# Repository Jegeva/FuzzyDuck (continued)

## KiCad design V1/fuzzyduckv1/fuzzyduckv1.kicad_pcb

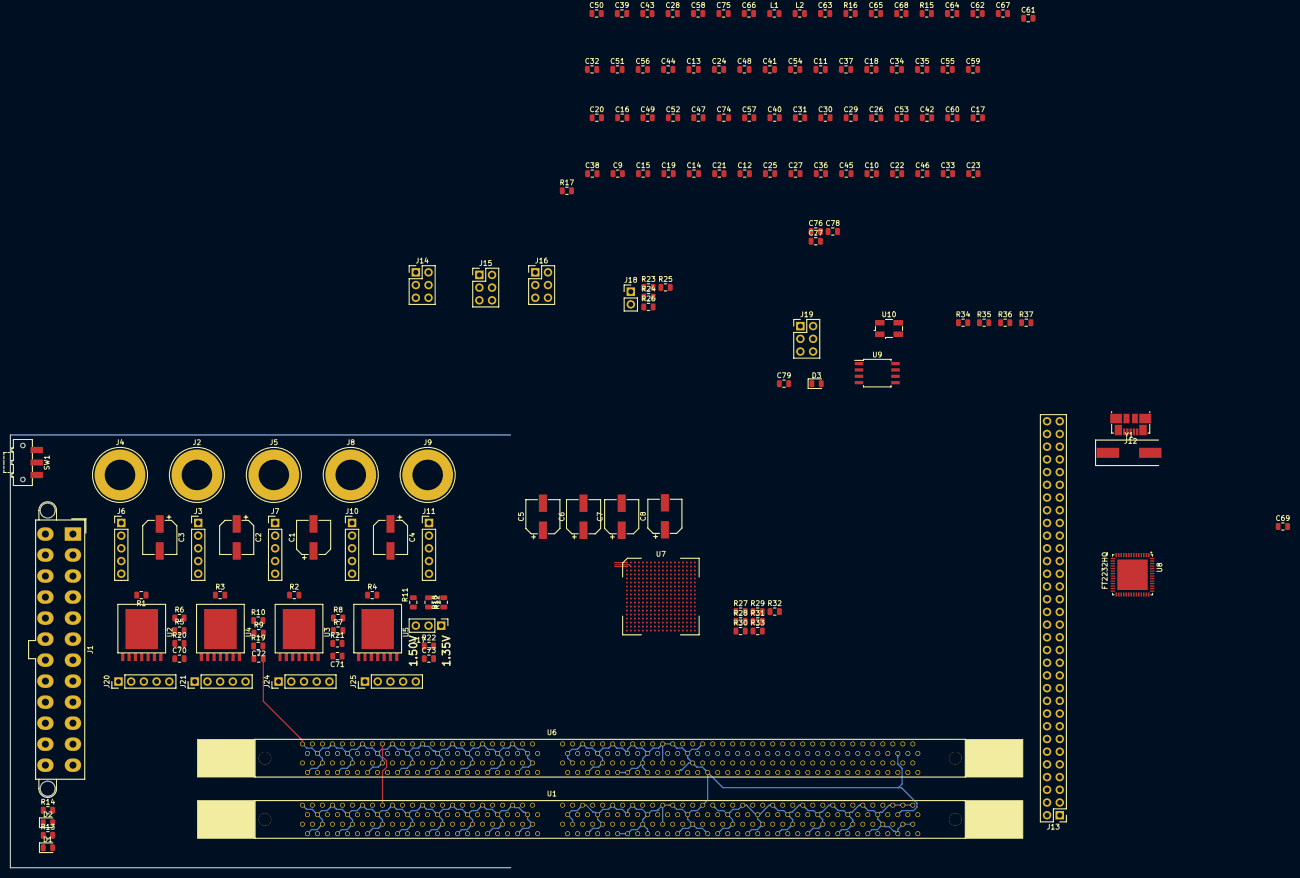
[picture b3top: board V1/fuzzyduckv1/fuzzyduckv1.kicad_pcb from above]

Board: 6 copper layers, 156 parts (0 on the bottom side), 268 nets.

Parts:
C1, C2, C3, C4, C5, C6, C7, C8: 200uF Electrolytic; CP_Elec_6.3x5.4_Nichicon
C9, C10, C11, C77: 47uF X7R; C_0805_2012Metric
C12, C70, C71, C72, C73: 10uF X7R; C_0805_2012Metric
C13, C14, C15, C16: 1uF X7R; C_0805_2012Metric
C17, C18, C19, C20, C21, C22, C23, C24, C25, C26, C27, C28, C29, C30, C31, C32, C33, C34, C35, C36, C37, C38, C39, C40, C41, C42, C43, C44: 100nF X7R; C_0805_2012Metric
C45, C46, C47, C48, C49, C50, C51, C52, C53, C54, C55, C56, C57, C58, C59, C60, C78: 10nF X7R; C_0805_2012Metric
C61, C64: 4.7uF TA; C_0805_2012Metric
C62, C65, C75: 100nF; C_0805_2012Metric
C63, C66, C74: 10nF; C_0805_2012Metric
C67, C68: 20pF; C_0805_2012Metric
C69: 3.3uF; C_0805_2012Metric
C76: 470nF X7R; C_0805_2012Metric
C79: 0.1uF X7R; C_0805_2012Metric
D1, D2, D3: LED; LED_0805_2012Metric
J1: Conn_02x12_Top_Bottom; Molex_Mini-Fit_Jr_5566-24A2_2x12_P4.20mm_Vertical
J2, J4, J5, J8, J9: Conn_01x01_Male; Banana_Jack_1Pin
J3, J6, J7, J10, J11, J20, J21, J24, J25: Conn_01x05; PinHeader_1x05_P2.54mm_Vertical
J12: USB_B_Micro; USB_Micro-B_Molex_47346-0001
J13: Conn_02x32_Odd_Even; PinHeader_2x32_P2.54mm_Vertical
J14, J15, J16, J19: Conn_02x03_Odd_Even; PinHeader_2x03_P2.54mm_Vertical
J17: Conn_01x03_Male; PinHeader_1x03_P2.54mm_Vertical
J18: Conn_01x02_Male; PinHeader_1x02_P2.54mm_Vertical
L1, L2: 600R/100MHz; L_0805_2012Metric
R1, R2, R3, R4: 100k; R_0805_2012Metric
R5, R6, R7, R9, R11: 10K 0.1%; R_0805_2012Metric
R8: 3.83K 0.1%; R_0805_2012Metric
R10: 7.15K 0.1%; R_0805_2012Metric
R12: 5K 0.5%; R_0805_2012Metric
R13, R14: 220; R_0805_2012Metric
R15: 12k; R_0805_2012Metric
R16, R34, R35, R36, R37: 1k; R_0805_2012Metric
R17: 10k; R_0805_2012Metric
R18: 5.9K 0.5%; R_0805_2012Metric
R19, R22: 120; R_0805_2012Metric
R20, R30, R31: 100; R_0805_2012Metric
R21: 180; R_0805_2012Metric
R23, R24, R25, R26, R27, R28, R32, R33: 4.7k; R_0805_2012Metric
R29: 50; R_0805_2012Metric
SW1: SW_SPDT; SW_SPDT_CK-JS102011SAQN
U1, U6: DIMM-240-DDR3; TE-1932000-DIMM-240
U2, U3, U4, U5: MIC69502
U7: XC7A35T-CSG324; BGA-324_15.0x15.0mm_Layout18x18_P0.8mm_Ball0.5mm_Pad0.4mm_N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
U8: FT2232HQ; VQFN-56-ftdi2232h-56q
U9: IS25LP128F; SOIJ-8_5.3x5.3mm_P1.27mm
U10: SiT8008B-100MHz; Crystal_SMD_EuroQuartz_MJ-4Pin_5.0x3.2mm
Y1: Crystal; Crystal_SMD_HC49-SD

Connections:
+1.0V: C5.1, C9.1, C13.1, C17.1, C21.1, C25.1, C29.1, C33.1, C37.1, C41.1, C45.1, C49.1, C53.1, C57.1, C70.1, J20.1, J20.2, J20.3, J20.4, J20.5, R5.1, R20.1, U2.5, U2.6, U7.F8, U7.F10, U7.G7, U7.G9, U7.G11, U7.H8, U7.J7, U7.J11, U7.K8, U7.L7, U7.L11, U7.M8, U7.M10, U7.N7, U7.N9, U7.N11
+1.2V: C7.1, C11.1, C15.1, C19.1, C23.1, C27.1, C31.1, C35.1, C39.1, C43.1, C47.1, C51.1, C55.1, C59.1, C72.1, J14.2, J15.2, J16.2, J19.2, J21.1, J21.2, J21.3, J21.4, J21.5, R9.1, R19.1, U4.5, U4.6
+1.5v: C8.1, C12.1, C16.1, C20.1, C24.1, C28.1, C32.1, C36.1, C40.1, C44.1, C48.1, C52.1, C56.1, C60.1
+1.8V: C6.1, C10.1, C14.1, C18.1, C22.1, C26.1, C30.1, C34.1, C38.1, C42.1, C46.1, C50.1, C54.1, C58.1, C71.1, J24.1, J24.2, J24.3, J24.4, J24.5, R7.1, R21.1, U3.5, U3.6, U7.E8, U7.F12, U7.H12, U7.K12, U7.M12
+3.3V: C76.1, C77.1, C79.2, J1.1, J1.2, J1.12, J1.13, J8.1, J10.1, J10.2, J10.3, J10.4, J10.5, J14.6, J15.6, J16.6, J19.6, L1.1, L2.1, R16.2, R23.1, R25.1, R26.1, R27.2, R30.1, R32.1, R33.1, U7.L17, U7.N13, U7.P16, U7.R9, U7.T12, U7.U15, U7.V18, U8.16, U8.36, U8.44, U8.50, U9.8, U10.4
+5V: C1.1, C2.1, C3.1, C4.1, J1.4, J1.6, J1.21, J1.22, J1.23, J5.1, J7.1, J7.2, J7.3, J7.4, J7.5, U2.2, U2.3, U3.2, U3.3, U4.2, U4.3, U5.2, U5.3
+12V: J1.10, J1.11, J2.1, J3.1, J3.2, J3.3, J3.4, J3.5
-12V: J1.14, J4.1, J6.1, J6.2, J6.3, J6.4, J6.5
ATX_POWEROK: J1.8, R1.2, R2.2, R3.2, R4.2, R14.2
CLK_100MHZ: U7.L18, U10.3
DDR_COM_A0: U1.188, U6.188, U7.B4
DDR_COM_A1: U1.181, U6.181, U7.A4
DDR_COM_A2: U1.61, U6.61, U7.A3
DDR_COM_A3: U1.180, U6.180, U7.B1
DDR_COM_A4: U1.59, U6.59, U7.A1
DDR_COM_A5: U1.58, U6.58, U7.B3
DDR_COM_A6: U1.178, U6.178, U7.B2
DDR_COM_A7: U1.56, U6.56, U7.D5
DDR_COM_A8: U1.177, U6.177, U7.D4
DDR_COM_A9: U1.175, U6.175, U7.E3
DDR_COM_A10: U1.70, U6.70, U7.D3
DDR_COM_A11: U1.55, U6.55, U7.F4
DDR_COM_A12: U1.174, U6.174, U7.F3
DDR_COM_A13: U1.196, U6.196, U7.E2
DDR_COM_A14: U1.172, U6.172, U7.D2
DDR_COM_A15: U1.171, U6.171, U7.H2
DDR_COM_BA0: U1.71, U6.71, U7.G2
DDR_COM_BA1: U1.190, U6.190, U7.C2
DDR_COM_BA2: U1.52, U6.52, U7.C1
DDR_COM_CAS#: U1.74, U6.74, U7.G14
DDR_COM_CB0: U1.39, U6.39, U7.E15
DDR_COM_CB1: U1.40, U6.40, U7.E16
DDR_COM_CB2: U1.45, U6.45, U7.D15
DDR_COM_CB3: U1.46, U6.46, U7.C15
DDR_COM_CB4: U1.158, U6.158, U7.H16
DDR_COM_CB5: U1.159, U6.159, U7.G16
DDR_COM_CB6: U1.164, U6.164, U7.F15
DDR_COM_CB7: U1.165, U6.165, U7.F16
DDR_COM_DQ0: U1.3, U6.3, U7.K6
DDR_COM_DQ1: U1.4, U6.4, U7.L1
DDR_COM_DQ2: U1.9, U6.9, U7.M1
DDR_COM_DQ3: U1.10, U6.10, U7.K3
DDR_COM_DQ4: U1.122, U6.122, U7.L3
DDR_COM_DQ5: U1.123, U6.123, U7.N2
DDR_COM_DQ6: U1.128, U6.128, U7.N1
DDR_COM_DQ7: U1.129, U6.129, U7.M3
DDR_COM_DQ8: U1.12, U6.12, U7.M2
DDR_COM_DQ9: U1.13, U6.13, U7.K5
DDR_COM_DQ10: U1.18, U6.18, U7.L4
DDR_COM_DQ11: U1.19, U6.19, U7.L6
DDR_COM_DQ12: U1.131, U6.131, U7.L5
DDR_COM_DQ13: U1.132, U6.132, U7.U1
DDR_COM_DQ14: U1.137, U6.137, U7.V1
DDR_COM_DQ15: U1.138, U6.138, U7.U4
DDR_COM_DQ16: U1.21, U6.21, U7.U3
DDR_COM_DQ17: U1.22, U6.22, U7.U2
DDR_COM_DQ18: U1.27, U6.27, U7.V2
DDR_COM_DQ19: U1.28, U6.28, U7.V5
DDR_COM_DQ20: U1.140, U6.140, U7.V4
DDR_COM_DQ21: U1.141, U6.141, U7.R3
DDR_COM_DQ22: U1.146, U6.146, U7.T3
DDR_COM_DQ23: U1.147, U6.147, U7.T5
DDR_COM_DQ24: U1.30, U6.30, U7.T4
DDR_COM_DQ25: U1.31, U6.31, U7.N5
DDR_COM_DQ26: U1.36, U6.36, U7.P5
DDR_COM_DQ27: U1.37, U6.37, U7.P4
DDR_COM_DQ28: U1.149, U6.149, U7.P3
DDR_COM_DQ29: U1.150, U6.150, U7.P2
DDR_COM_DQ30: U1.155, U6.155, U7.R2
DDR_COM_DQ31: U1.156, U6.156, U7.M4
DDR_COM_DQ32: U1.81, U6.81, U7.N4
DDR_COM_DQ33: U1.82, U6.82, U7.R1
DDR_COM_DQ34: U1.87, U6.87, U7.T1
DDR_COM_DQ35: U1.88, U6.88, U7.M6
DDR_COM_DQ36: U1.200, U6.200, U7.N6
DDR_COM_DQ37: U1.201, U6.201, U7.R6
DDR_COM_DQ38: U1.206, U6.206, U7.R5
DDR_COM_DQ39: U1.207, U6.207, U7.V7
DDR_COM_DQ40: U1.90, U6.90, U7.V6
DDR_COM_DQ41: U1.91, U6.91, U7.U9
DDR_COM_DQ42: U1.96, U6.96, U7.V9
DDR_COM_DQ43: U1.97, U6.97, U7.U7
DDR_COM_DQ44: U1.209, U6.209, U7.U6
DDR_COM_DQ45: U1.210, U6.210, U7.R7
DDR_COM_DQ46: U1.215, U6.215, U7.T6
DDR_COM_DQ47: U1.216, U6.216, U7.R8
DDR_COM_DQ48: U1.99, U6.99, U7.T8
DDR_COM_DQ49: U1.100, U6.100, U7.U8
DDR_COM_DQ50: U1.105, U6.105, U7.F5
DDR_COM_DQ51: U1.106, U6.106, U7.C6
DDR_COM_DQ52: U1.218, U6.218, U7.C5
DDR_COM_DQ53: U1.219, U6.219, U7.B7
DDR_COM_DQ54: U1.224, U6.224, U7.B6
DDR_COM_DQ55: U1.225, U6.225, U7.A6
DDR_COM_DQ56: U1.108, U6.108, U7.A5
DDR_COM_DQ57: U1.109, U6.109, U7.D8
DDR_COM_DQ58: U1.114, U6.114, U7.C7
DDR_COM_DQ59: U1.115, U6.115, U7.E6
DDR_COM_DQ60: U1.227, U6.227, U7.E5
DDR_COM_DQ61: U1.228, U6.228, U7.E7
DDR_COM_DQ62: U1.233, U6.233, U7.D7
DDR_COM_DQ63: U1.234, U6.234, U7.C4
DDR_COM_DQS0: U1.7, U6.7, U7.H1
DDR_COM_DQS0#: U1.6, U6.6, U7.G1
DDR_COM_DQS1: U1.16, U6.16, U7.F1
DDR_COM_DQS1#: U1.15, U6.15, U7.E1
DDR_COM_DQS2: U1.25, U6.25, U7.G6
DDR_COM_DQS2#: U1.24, U6.24, U7.F6
DDR_COM_DQS3: U1.34, U6.34, U7.G4
DDR_COM_DQS3#: U1.33, U6.33, U7.G3
DDR_COM_DQS4: U1.85, U6.85, U7.J4
DDR_COM_DQS4#: U1.84, U6.84, U7.H4
DDR_COM_DQS5: U1.94, U6.94, U7.J3
DDR_COM_DQS5#: U1.93, U6.93, U7.J2
DDR_COM_DQS6: U1.103, U6.103, U7.K2
DDR_COM_DQS6#: U1.102, U6.102, U7.K1
DDR_COM_DQS7: U1.112, U6.112, U7.H6
DDR_COM_DQS7#: U1.111, U6.111, U7.H5
DDR_COM_DQS8: U1.43, U6.43, U7.D14
DDR_COM_DQS8#: U1.42, U6.42, U7.C14
DDR_COM_DQS9: U1.125, U6.125, U7.B13
DDR_COM_DQS9#: U1.126, U6.126, U7.B14
DDR_COM_DQS10: U1.134, U6.134, U7.C12
DDR_COM_DQS10#: U1.135, U6.135, U7.B12
DDR_COM_DQS11: U1.143, U6.143, U7.B11
DDR_COM_DQS11#: U1.144, U6.144, U7.A11
DDR_COM_DQS12: U1.152, U6.152, U7.F13
DDR_COM_DQS12#: U1.153, U6.153, U7.F14
DDR_COM_DQS13: U1.203, U6.203, U7.D12
DDR_COM_DQS13#: U1.204, U6.204, U7.D13
DDR_COM_DQS14: U1.212, U6.212, U7.B16
DDR_COM_DQS14#: U1.213, U6.213, U7.B17
DDR_COM_DQS15: U1.221, U6.221, U7.A15
DDR_COM_DQS15#: U1.222, U6.222, U7.A16
DDR_COM_DQS16: U1.230, U6.230, U7.A13
DDR_COM_DQS16#: U1.231, U6.231, U7.A14
DDR_COM_DQS17: U1.161, U6.161, U7.B18
DDR_COM_DQS17#: U1.162, U6.162, U7.A18
DDR_COM_ERROUT#: U1.53, U6.53, U7.D17
DDR_COM_EVENT#: U1.187, U6.187, U7.K13
DDR_COM_RAS#: U1.192, U6.192, U7.H14
DDR_COM_RPARIN: U1.68, U6.68, U7.E17
DDR_COM_WE#: U1.73, U6.73, U7.J13
DDR_DIMM0_CK0: U1.184, U7.F18
DDR_DIMM0_CK0#: U1.185, U7.J17
DDR_DIMM0_CK1: U1.63, U7.D18
DDR_DIMM0_CK1#: U1.64, U7.G18
DDR_DIMM0_CKE0: U1.50, U7.J18
DDR_DIMM0_CKE1: U1.169, U7.K15
DDR_DIMM0_ODT0: U1.195, U7.C17
DDR_DIMM0_ODT1: U1.77, U7.C16
DDR_DIMM0_RESET#: U1.168, U7.E18
DDR_DIMM0_S0#: U1.193, U7.H17
DDR_DIMM0_S1#: U1.76, U7.G17
DDR_DIMM0_S2#: U1.79, U7.J14
DDR_DIMM0_S3#: U1.198, U7.H15
DDR_DIMM1_CK0: U6.184, U7.C10
DDR_DIMM1_CK0#: U6.185, U7.A10
DDR_DIMM1_CK1: U6.63, U7.A8
DDR_DIMM1_CK1#: U6.64, U7.C11
DDR_DIMM1_CKE0: U6.50, U7.A9
DDR_DIMM1_CKE1: U6.169, U7.D10
DDR_DIMM1_ODT0: U6.195, U7.B8
DDR_DIMM1_ODT1: U6.77, U7.B9
DDR_DIMM1_RESET#: U6.168, U7.G13
DDR_DIMM1_S0#: U6.193, U7.J15
DDR_DIMM1_S1#: U6.76, U7.K16
DDR_DIMM1_S2#: U6.79, U7.D9
DDR_DIMM1_S3#: U6.198, U7.C9
DDR_SCL: U1.118, U6.118
DDR_SDA: U1.238, U6.238
DDR_VCC: C73.1, J14.4, J15.4, J16.4, J19.4, R11.1, R17.1, R22.1, R34.1, R36.1, U1.51, U1.54, U1.57, U1.60, U1.62, U1.65, U1.66, U1.69, U1.72, U1.75, U1.78, U1.170, U1.173, U1.176, U1.179, U1.182, U1.183, U1.186, U1.189, U1.191, U1.194, U1.197, U1.236, U5.5, U5.6, U6.51, U6.54, U6.57, U6.60, U6.62, U6.65, U6.66, U6.69, U6.72, U6.75, U6.78, U6.170, U6.173, U6.176, U6.179, U6.182, U6.183, U6.186, U6.189, U6.191, U6.194, U6.197, U6.236
FLASH_IO0: U7.K17, U9.5
FLASH_IO1: U7.K18, U9.2
FLASH_IO2: U7.L14, U9.3
FLASH_IO3: U7.M14, U9.7
FLASH_SCK: R29.2, U7.E9, U9.6
FLASH_SS#: U7.L13, U9.1
FPGA_CTS#: J13.40, U7.M13
FPGA_DCD#: J13.46, U7.N14
FPGA_DSR#: J13.44, U7.T18
FPGA_DTR#: J13.42, U7.R18
FPGA_RI#: J13.48, U7.P14
FPGA_RTS#: J13.38, U7.R13
FPGA_RX_D: J13.34, U7.M18
FPGA_TX_D: J13.36, U7.R12
GND: C1.2, C2.2, C3.2, C4.2, C5.2, C6.2, C7.2, C8.2, C9.2, C10.2, C11.2, C12.2, C13.2, C14.2, C15.2, C16.2, C17.2, C18.2, C19.2, C20.2, C21.2, C22.2, C23.2, C24.2, C25.2, C26.2, C27.2, C28.2, C29.2, C30.2, C31.2, C32.2, C33.2, C34.2, C35.2, C36.2, C37.2, C38.2, C39.2, C40.2, C41.2, C42.2, C43.2, C44.2, C45.2, C46.2, C47.2, C48.2, C49.2, C50.2, C51.2, C52.2, C53.2, C54.2, C55.2, C56.2, C57.2, C58.2, C59.2, C60.2, C61.2, C62.2, C63.2, C64.2, C65.2, C66.2, C67.2, C68.2, C69.2, C70.2, C71.2, C72.2, C73.2, C76.2, C77.2, C79.1, D1.1, D2.1, D3.1, J1.3, J1.5, J1.7, J1.15, J1.17, J1.18, J1.19, J1.24, J9.1, J11.1, J11.2, J11.3, J11.4, J11.5, J12.5, J12.6, J18.1, R6.2, R8.2, R10.2, R12.1, R15.2, R18.1, R19.2, R20.2, R21.2, R22.2, R24.1, R28.2, R35.1, R37.1, SW1.3, U1.2, U1.5, U1.8, U1.11, U1.14, U1.17, U1.20, U1.23, U1.26, U1.29, U1.32, U1.35, U1.38, U1.41, U1.44, U1.47, U1.80, U1.83, U1.86, U1.89, U1.92, U1.95, U1.98, U1.101, U1.104, U1.107, U1.110, U1.113, U1.116, U1.117, U1.119, U1.121, U1.124, U1.127, U1.130, U1.133, U1.136, U1.139, U1.142, U1.145, U1.148, U1.151, U1.154, U1.157, U1.160, U1.163, U1.166, U1.199, U1.202, U1.205, U1.208, U1.211, U1.214, U1.217, U1.220, U1.223, U1.226, U1.229, U1.232, U1.235, U1.237, U1.239, U2.4, U3.4, U4.4, U5.4, U6.2, U6.5, U6.8, U6.11, U6.14, U6.17, U6.20, U6.23, U6.26, U6.29, U6.32, U6.35, U6.38, U6.41, U6.44, U6.47, U6.80, U6.83, U6.86, U6.89, U6.92, U6.95, U6.98, U6.101, U6.104, U6.107, U6.110, U6.113, U6.116, U6.119, U6.121, U6.124, U6.127, U6.130, U6.133, U6.136, U6.139, U6.142, U6.145, U6.148, U6.151, U6.154, U6.157, U6.160, U6.163, U6.166, U6.199, U6.202, U6.205, U6.208, U6.211, U6.214, U6.217, U6.220, U6.223, U6.226, U6.229, U6.232, U6.235, U6.237, U6.239, U7.A2, U7.A12, U7.B5, U7.B15, U7.C8, U7.C18, U7.D1, U7.D11, U7.E4, U7.E14, U7.F7, U7.F9, U7.F11, U7.F17, U7.G8, U7.G10, U7.G12, U7.H3, U7.H7, U7.H11, U7.H13, U7.J6, U7.J8, U7.J12, U7.J16, U7.K7, U7.K11, U7.L2, U7.L8, U7.L9, U7.L10, U7.L12, U7.M5, U7.M7, U7.M9, U7.M11, U7.M15, U7.N8, U7.N10, U7.N12, U7.N18, U7.P1, U7.R4, U7.R14, U7.T7, U7.T17, U7.U10, U7.V3, U7.V13, U8.10, U8.21, U8.41, U8.45, U9.4, U10.2
unnamed: C61.1, C62.1, C63.1, L2.2, U8.5
unnamed: C64.1, C65.1, C66.1, L1.2, U8.9
unnamed: C67.1, U8.3, Y1.1
unnamed: C68.1, U8.4, Y1.2
unnamed: C69.1, U8.2, U8.31, U8.43
unnamed: C78.1, U7.K10
unnamed: C78.2, U7.J9
unnamed: D1.2, R13.1
unnamed: D2.2, R14.1
unnamed: D3.2, R31.1
unnamed: J1.9, R13.2
unnamed: J1.16, SW1.2
unnamed: J12.2, U8.7
unnamed: J12.3, U8.8
unnamed: J13.1, U8.12
unnamed: J13.3, U8.13
unnamed: J13.5, U8.14
unnamed: J13.7, U8.15
unnamed: J13.9, U8.17
unnamed: J13.11, U8.18
unnamed: J13.13, U8.19
unnamed: J13.15, U8.20
unnamed: J13.17, U8.22
unnamed: J13.19, U8.23
unnamed: J13.21, U8.24
unnamed: J13.23, U8.25
unnamed: J13.25, U8.26
unnamed: J13.27, U8.27
unnamed: J13.29, U8.28
unnamed: J13.31, U8.29
unnamed: J13.33, U8.32
unnamed: J13.35, U8.33
unnamed: J13.37, U8.34
unnamed: J13.39, U8.35
unnamed: J13.41, U8.37
unnamed: J13.43, U8.38
unnamed: J13.45, U8.39
unnamed: J13.47, U8.40
unnamed: J13.49, U8.42
unnamed: J13.51, U8.46
unnamed: J13.53, U8.47
unnamed: J13.55, U8.48
unnamed: J13.57, U8.49
unnamed: J13.59, U8.51
unnamed: J13.61, U8.52
unnamed: J13.63, U8.53
unnamed: J17.1, R18.2
unnamed: J17.2, R11.2, U5.7
unnamed: J17.3, R12.2
unnamed: J18.2, R26.2, U7.P11
unnamed: R1.1, U2.1
unnamed: R2.1, U3.1
unnamed: R3.1, U4.1
unnamed: R4.1, U5.1
unnamed: R5.2, R6.1, U2.7
unnamed: R7.2, R8.1, U3.7
unnamed: R9.2, R10.1, U4.7
unnamed: R15.1, U8.6
unnamed: R16.1, U8.11
unnamed: R17.2, U6.117
unnamed: R23.2, U7.P12
unnamed: R24.2, U7.P13
unnamed: R25.2, U7.P8
unnamed: R27.1, R28.1, U7.L15
unnamed: R29.1, U7.L16
unnamed: R30.2, R31.2, U7.P10
unnamed: R32.2, U7.P7
unnamed: R33.2, U7.P9
unnamed: R34.2, R35.2, U1.1, U1.48, U1.49, U1.67, U1.120, U1.240
unnamed: R36.2, R37.2, U6.1, U6.48, U6.49, U6.67, U6.120, U6.240
TCK: J13.2, U7.E10
TDI_FPGA: J13.4, U7.E11
TDO_JPGA: J13.6, U7.E13
TMS: J13.8, U7.E12
VCCO_15: J16.1, J16.3, J16.5, U7.A17, U7.C13, U7.D16, U7.G15, U7.H18, U7.K14
VCCO_16: J14.1, J14.3, J14.5, U7.B10
VCCO_34: J15.5, U7.K4, U7.N3, U7.P6, U7.T2, U7.U5, U7.V8
VCCO_35: J19.5, U7.A7, U7.C3, U7.D6, U7.F2, U7.G5, U7.J1
VCC_DDR: J25.1, J25.2, J25.3, J25.4, J25.5
XADC_GND: C74.1, C75.1, U7.H9
XADC_VCC: C74.2, C75.2, U7.H10

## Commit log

2021-03-22 First egg
